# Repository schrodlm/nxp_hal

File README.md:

# Assignment 5: HAL development on S32K118

In this assignment the target platform changes from the STM32F407 to the NXP S32K118, an Arm Cortex‑M0+ microcontroller from the S32K1xx automotive family. On STM32, STM32CubeMX generated both the initialization code and a Hardware Abstraction Layer (HAL). On the S32K118, no vendor HAL is provided: you are given the CMSIS‑style register definitions and a minimal project skeleton, and the objective of this assignment is to implement the HAL yourself.

For every peripheral used in the exercises, a header file with a complete Doxygen description of the API (functions, parameters, preconditions, pin mapping) is supplied. Your task is to implement the corresponding `.c` files so that the provided example programs in `main.c` behave as specified.

---

## 0. Before you start — board preparation

> ⚠️ Before powering the board on and before flashing anything, the board jumpers must be reconfigured for the S32K118:
>
> - move the **STM** jumper to the **OFF** position (disables the STM32 side by keeping it all the time in reset);
> - move the **S32** jumper to the **RST** position (connects the reset signal on S32 to the reset button on the board).
> - connect the board via a USB-C
> Once this is done, the STM32 development board may remain physically attached to the shield — it does not interfere with the sensors/actuators.

The exact jumper locations are shown in the board schematic and in the KiCad project under [`ers-board-v1.2/`](ers-board-v1.2/). See in particular [`ers-board-v1.2/schematics.pdf`](ers-board-v1.2/schematics.pdf) and the KiCad sources under [`ers-board-v1.2/kicad/`](ers-board-v1.2/kicad/) [`210_prog_soft_start.kicad_sch`](ers-board-v1.2/kicad/210_prog_soft_start.kicad_sch) for the programmer/reset‑related jumpers, and the other sheets for the peripheral pin assignments referenced by the HAL headers.

---

## 1. Project contents

The project is self‑contained and is organized as follows (simplified):

```text
├── CMakeLists.txt              # top-level build script
├── devices/                    # CMSIS headers, startup code, linker script
│   ├── common/s32_core_cm0.h   
│   ├── S32K118/…               # register definitions, linker scripts, SVD
│   ├── device_registers.h
│   ├── callbacks.h
│   ├── devassert.h
│   ├── floats.h
│   ├── status.h
│   └── startup.c / .h
├── src/
│   ├── core/                   # provided: clock, systick, UART, syscalls
│   │   ├── clock.c / .h
│   │   ├── systick.c / .h
│   │   ├── syscalls.c / .h
│   │   ├── debug_uart.c / .h
│   │   └── system.c / .h       # system_init() convenience
│   ├── lib/                    # to be implemented: only the .h files are given
│   │   ├── led.h               # implement led.c
│   │   ├── btn.h               # implement btn.c
│   │   ├── btn_cnt.h           # implement btn_cnt.c
│   │   ├── kpad.h              # implement kpad.c
│   │   ├── enc.h               # implement enc.c
│   │   ├── servo.h             # implement servo.c
│   │   ├── spi.h               # implement spi.c
│   │   ├── lcd.h               # implement lcd.c
│   │   ├── lcd_font.c / .h     # provided (bitmap font)
│   │   ├── eeprom.h            # implement eeprom.c
│   │   ├── joy.h               # implement joy.c
│   │   └── sht40.h             # implement sht40.c
│   ├── e00_starter/main.c      # runs out-of-the-box, no HAL needed
│   ├── e01_led/main.c          # requires led.c
│   ├── e02_btn/main.c          # requires led.c, btn.c
│   ├── e03_btn_cnt/main.c      # requires led.c, btn.c, btn_cnt.c
│   ├── e04_kpad/main.c         # requires led.c, kpad.c
│   ├── e05_enc/main.c          # requires led.c, enc.c
│   ├── e06_servo/main.c        # requires led.c, enc.c, servo.c
│   ├── e07_lcd/main.c          # requires led.c, spi.c, lcd.c
│   ├── e08_eeprom/main.c       # requires led.c, spi.c, eeprom.c
│   ├── e09_joy/main.c          # requires led.c, joy.c
│   └── e10_sht/main.c          # requires several of the above and sht40.c
├── docs/                       # S32K118 reference manual and CPU documentation
└── unity/                      # Unity test framework (for the test targets)
```

Provided:

- [`devices/`](devices/) — NXP CMSIS register headers, startup code, and the GCC linker script.
- [`src/core/`](src/core/) — clock at 40 MHz, SysTick at 1 ms, debug UART (`printf` over LPUART1 at 1 Mbps), and syscalls. Calling `system_init()` performs all of this.
- [`src/lib/lcd_font.{c,h}`](src/lib/lcd_font.c) — 5×7 bitmap font used by the LCD driver.
- [`src/eXX_*/main.c`](src/) — the `main.c` of every exercise.
- [`CMakeLists.txt`](CMakeLists.txt) — all build targets, including flashing targets (`UP_*`).

To be implemented:

- One `.c` file per peripheral under [`src/lib/`](src/lib), implementing the API documented in the corresponding header. The header files contain the full specification (pin mapping, required behavior, preconditions, ISR contracts, and so on) and should be read carefully before starting.

No new `main.c` is to be written.

---

## 2. Toolchain

Two tools are required: an ARM GCC toolchain (for cross‑compilation) and OpenOCD (for flashing and debugging).

> A recent OpenOCD (version ≥ 0.12.0+dev – from 2026) is required. Older distribution packages frequently lack correct support for the S32K target. Prebuilt releases are available from <https://github.com/openocd-org/openocd/releases>.

In addition, CMake (≥ 3.20) and a build driver (Ninja is recommended; `make` is also supported) are required.

> The use of an IDE with integrated CMake support, such as CLion or Visual Studio Code (with the *CMake Tools* and *Cortex‑Debug* extensions), is strongly recommended. CLion ships its own bundled copies of CMake and Ninja, so under CLion only the ARM GCC toolchain and OpenOCD have to be installed separately. Both IDEs provide integrated support for GDB + OpenOCD debugging.

### 2.1 Windows

1. ARM GCC toolchain — install the standalone [Arm GNU Toolchain](https://developer.arm.com/downloads/-/arm-gnu-toolchain-downloads) (the `arm-none-eabi` package). Alternatively, it can be installed via the [Scoop](https://scoop.sh/) package manager: `scoop install gcc-arm-none-eabi`. Students who already have STM32CubeCLT installed from a previous assignment do not need to install anything else, since STM32CubeCLT ships `arm-none-eabi-gcc` and `arm-none-eabi-gdb` as part of its distribution.
2. OpenOCD — download the latest Windows build from the GitHub releases page listed above, extract the archive, and add its `bin/` directory to `PATH` (or invoke the executable with its full path).

### 2.2 Linux

Install the ARM GCC toolchain via your distribution's package manager (the package name varies between distributions; on Debian/Ubuntu it is `gcc-arm-none-eabi`).

---

## 3. Build system and workflow

The project uses CMake with the cross‑compilation toolchain configured directly inside `CMakeLists.txt` (which forces `arm-none-eabi-gcc` and links against the S32K118 linker script). The recommended way of working with the project is to open it as a CMake project in CLion or VS Code and let the IDE drive the configuration, build, and flashing steps.

### 3.1 Build targets

For each exercise target `eXX_name`, the build produces:

- `eXX_name.elf` — ELF file with debug symbols (consumed by GDB);
- `eXX_name.hex` — Intel HEX file (consumed by the flashing command);
- `eXX_name.map` — linker map;
- `eXX_name.asm` — full disassembly listing, useful for diagnosing subtle HAL issues.

### 3.2 Flashing the board

The development board is connected via CMSIS‑DAP over SWD. Each exercise defines an auto‑generated flashing target named `UP_<target>.elf` (for example, `UP_e00_starter.elf`). Building this target from the IDE builds the corresponding exercise, programs the flash, verifies the content, and resets the microcontroller. (The `UP_*` targets are custom CMake targets — they are *built*, not run. In CLion and VS Code, select the target from the target selector and invoke the usual *build* command.)

### 3.3 Serial output

`printf()` is routed to LPUART1 (pins PTC7/TX and PTC6/RX) at 1 Mbps, 8N1 by `debug_uart_init()`, which is invoked from `system_init()`.

A USB‑to‑UART adapter must be connected to these pins and a terminal application (for example PuTTY, Tera Term, `minicom`, `picocom`, or the VS Code *Serial Monitor* extension) configured for 1 000 000 baud, 8N1, no flow control.

### 3.4 Unit tests

Several modules (`e01_led`, `e02_btn`, `e03_btn_cnt`, `e08_eeprom`) are accompanied by a companion `test.c` that runs on the board. The tests are written against [Unity](https://www.throwtheswitch.org/unity), a small C unit‑testing framework designed for embedded targets. Each test file defines a set of `test_*` functions and registers them with `RUN_TEST(...)` inside `main`; Unity executes them sequentially, compares actual and expected values via `TEST_ASSERT_*` macros, and prints a `PASS`/`FAIL` line per test together with a summary of the whole run. The framework itself lives under `unity/` and is linked automatically into every test binary.

The corresponding binaries are exposed through the `TST_*` target prefix (for example, `UP_TST_e01_led.elf` builds and flashes the test variant of the LED exercise). Test results are printed on the debug UART. Some tests require an additional jumper wire; refer to the comments at the top of each `test.c` file for details.

### 3.5 Logging with `printf`

`printf` is the most immediate diagnostic instrument available and will be used throughout the assignment. The following points should be observed:

- Terminate each message with `\n` or call `fflush(stdout)` explicitly. The C runtime line‑buffers `stdout`, and a message without a newline may remain in the buffer and never be transmitted over the UART.
- Avoid calling `printf` from interrupt service routines. LPUART1 blocks when its transmit FIFO is full, so a verbose ISR may stall the main loop. For ISRs, either set a flag and perform the output from the main loop, or restrict the output to a single character via `debug_uart_putchar()`.
- Do not use the `%f` conversion specifier. Use integer formatting (milli‑units or fixed‑point) instead.

### 3.6 Reference documentation

Several reference PDFs are provided under `examples/s32/docs/`. You will not need to read any of them cover to cover; each one is a lookup reference for a specific layer of the stack.

- [`S32K-RM.pdf`](docs/S32K-RM.pdf) — **S32K1xx Series Reference Manual.** The primary document for this assignment. Contains the description of every peripheral (GPIO/PORT, LPSPI, LPI2C, LPUART, LPIT, ADC, FTM, DMA/DMAMUX, FlexCAN, …) and the corresponding register maps, together with the **pin‑mux (PORT alternate‑function) tables** and the **DMAMUX source tables** (which DMA request number corresponds to which peripheral). The register names used in the manual match the macros in `devices/S32K118/include/S32K118.h`, so a chapter in this PDF translates directly to the register writes you need in your `.c` file. Consult it whenever you are configuring a new peripheral, wiring a pin to an alternate function, or hooking a peripheral to a DMA channel. **Note**: the reference manuals has a number of attachments, including S32K118 IO signal description input multiplexing and S32K1xx DMA interrupt mapping as excel files. To see the attachments, open the PDF in a capable viewer (for example, Foxit PDF Reader or Acrobat Reader) and look for the attachments pane.

- [`S32K1xx.pdf`](docs/S32K1xx.pdf) — **S32K1xx Data Sheet.** Electrical characteristics, memory map overview, clock tree, and package pin assignments. Useful for the electrical/timing side of things; the functional pin‑mux information is in `S32K-RM.pdf` (see above).
- `Arm_Architecture_v6m_Reference_Manual.pdf` — **ARMv6‑M Architecture Reference Manual.** Defines the instruction set, exception model, and programmer's model of the Cortex‑M0+ core. Needed only if you want to read or understand Thumb assembly (for example, the `.asm` listing produced by the build) or when dealing with low‑level exception behavior.
- [`DDI0484C_cortex_m0p_r0p1_trm.pdf`](docs/DDI0484C_cortex_m0p_r0p1_trm.pdf) — **Cortex‑M0+ Technical Reference Manual.** Implementation‑specific documentation of the CPU core (NVIC layout, SysTick, pipeline behavior). Relevant mainly when you are configuring the NVIC (interrupt enable/priority) or SysTick — both of which are already done for you in `core/`, but are worth consulting if you add your own interrupts.
- [`DUI0662B_cortex_m0p_r0p1_dgug.pdf`](docs/DUI0662B_cortex_m0p_r0p1_dgug.pdf) — **Cortex‑M0+ Devices Generic User Guide.** A tutorial‑style companion to the TRM, written from a programmer's point of view. Often a gentler starting point when the TRM is too dense.

In short: start from the corresponding header in `src/lib/`, look up the peripheral chapter (and the pin‑mux and DMAMUX tables) in `S32K-RM.pdf` and fall back to the Cortex‑M0+ documents only for core‑side questions (interrupts, exceptions, low‑level CPU behavior).

---

## 4. How to work on an exercise

Each HAL module should be implemented one at a time and verified with the corresponding exercise program. The recommended procedure for every exercise is:

1. Open the corresponding `.h` file in `src/lib/` and read the Doxygen description in full (pin mapping, expected behavior, whether functions may be called from ISR context, notes on listeners, and so on).
2. Consult the relevant peripheral chapter in the S32K118 Reference Manual (`docs/S32K-RM.pdf`). The register names in the manual match the macros in `devices/S32K118/include/S32K118.h`.
3. Create the `.c` file in `src/lib/`. No modification to `CMakeLists.txt` is required — the top‑level `CMakeLists.txt` already references the expected filenames.
4. Build the `UP_eXX_...elf` target to flash the corresponding exercise, and verify the behavior on the board and over UART.
5. If a unit test is provided for the module (see [§ 3.4](#34-unit-tests)), flash it by building the matching `UP_TST_eXX_...elf` target and confirm that all test cases pass on the debug UART. Executing the provided tests is a mandatory part of the assignment: a module counts as correctly implemented only once its test reports all `PASS`. Any additional wiring required by the test is documented at the top of the corresponding `test.c` file.

### 4.1 Using AI assistants

You are allowed to use AI coding assistants (Copilot, ChatGPT, Claude, Gemini, …) while working on this assignment, but the following conditions apply:

- **Review every register assignment manually.** AI models are trained on a huge variety of microcontroller families, and they routinely produce code that *looks* correct but encodes subtle mistakes. Always cross‑check the generated register configuration against the corresponding chapter of `docs/S32K-RM.pdf` before trusting it, especially for PORT `PCR` (MUX field), PCC clock gates, peripheral enable bits, DMAMUX source numbers, and NVIC settings.
- **You must be able to explain every register assignment in your code.** During evaluation you may be asked to walk through any line of any peripheral configuration. You will be given the relevant register map from the Reference Manual, so you do not have to memorise the register abbreviations and bit positions — but you are expected to explain, for every `PCC->PCCn[...] = …`, every `PORT->PCR[...] = …`, every `LPSPIx->CFGRx = …`, and so on, *why* those bits are set the way they are and what the resulting hardware behavior is. "The AI wrote it" is not an acceptable answer. If you cannot explain a line, treat that as a signal to go back and read the relevant section of the Reference Manual until you can.

---

## 5. Exercises

### Exercise 0 — Starter and environment verification

Target: `e00_starter`.

Goal: verify that the complete toolchain (build, flash, serial terminal, debugger) is functional before any HAL code is written. No HAL code is required for this exercise; only the provided `core` modules are used.

Expected behavior: once flashed, the board prints one line per second on the debug UART:

```text
[0000000003] Counter 0
[0000001003] Counter 1
[0000002003] Counter 2
…
```

If the output is garbled, verify that the terminal is configured for 1 Mbps. If there is no output at all, verify that the USB‑to‑UART adapter is wired to PTC7 and PTC6 and that no other device is driving these pins.

---

### Exercise 1 — LED

Target: `e01_led`. Module: `led.c`.

Goal: implement GPIO output control for the four on‑board LEDs. Verified by `e01_led` cycling through the LEDs one at a time.

Build the `UP_TST_e01_led.elf` target to flash and execute the unit test, and confirm that all cases report `PASS` on the debug UART.

---

### Exercise 2 — Buttons

Target: `e02_btn`. Module: `btn.c`.

Goal: implement GPIO input and PORT‑interrupt handling for the four on‑board buttons. Verified by `e02_btn` printing the button state on every edge.

Build the `UP_TST_e02_btn.elf` target to flash and execute the unit test, and confirm that all cases report `PASS` on the debug UART.

---

### Exercise 3 — Button counter with debouncing

Target: `e03_btn_cnt`. Module: `btn_cnt.c`.

Goal: implement a debounced press counter on top of `btn.c` and the SysTick listener mechanism, following the state machine described in `btn_cnt.h`. Verified by `e03_btn_cnt` reporting a stable count even under rapid repeated presses.

Build the `UP_TST_e03_btn_cnt.elf` target to flash and execute the unit test, and confirm that all cases report `PASS` on the debug UART.

---

### Exercise 4 — Matrix keypad

Target: `e04_kpad`. Module: `kpad.c`.

Goal: implement scanning of the external 3×4 matrix keypad. Verified by `e04_kpad` printing the set of pressed keys whenever it changes.

---

### Exercise 5 — Rotary encoder

Target: `e05_enc`. Module: `enc.c`.

Goal: implement quadrature decoding of the rotary encoder using FTM1, plus GPIO input for the encoder push button. Verified by `e05_enc` printing the encoder position and resetting it on button press.

---

### Exercise 6 — Servo motor

Target: `e06_servo`. Module: `servo.c`.

Goal: implement 50 Hz PWM control of the SG90 servo using FTM0. Verified by `e06_servo` driving the servo from the encoder position.

---

### Exercise 7 — SPI and ST7565 LCD

Modules: `spi.c`, `lcd.c`.

Goal: implement the SPI driver for LPSPI0 and the ST7565 graphical LCD driver on top of it.

This exercise is split into two phases and should be done in order:

1. **Blocking variant — target `e07_lcd`.** Start with the blocking SPI (`spi_txrx`) and the full framebuffer‑based drawing API. The implementation busy‑waits on the LPSPI `TDF`/`RDF` flags. Verified by `e07_lcd` showing a static text pattern and animated pixels.
2. **DMA variant — target `e07_lcd-dma` (OPTIONAL, for the daring ones).** Once the blocking variant works, add the DMA path (`spi_dma_txrx` plus the asynchronous path in `lcd.c`), compiled with the `SPI_WITH_DMA` definition that the `e07_lcd-dma` target already provides. The on‑screen behavior must be identical; the difference is that the main loop stays responsive during SPI transfers. **This phase is optional** — it is significantly more involved than the blocking variant, and students may skip it and move on to exercise 8.

Read `spi.h` carefully before starting the DMA phase — especially the instructions on the buffer alignment and byte‑swap.

#### How to build the DMA path

The DMA variant offloads the entire transfer to eDMA + LPSPI, so `spi_dma_txrx()` can return immediately and the caller is notified later via a callback. Before starting, read `spi.h` in full — it fixes the observable contract (non‑blocking semantics, 4‑byte buffer alignment, byte swap, split TX/RX callbacks). The implementation can then proceed roughly as follows:

1. **Two DMA channels.** Allocate one channel for TX (source = memory buffer, destination = `LPSPI0->TDR`) and one for RX (source = `LPSPI0->RDR`, destination = memory buffer). Route the LPSPI0 TX and RX requests to them via DMAMUX (sources 15 and 14) and enable LPSPI's DMA request generation with `DER = TDDE | RDDE`.

2. **4‑byte transfer granularity.** Program the eDMA TCDs with `SSIZE = DSIZE = 2` (meaning 2² = 4 bytes) and `NBYTES = 4`. The major‑loop iteration count is `count / 4`. This is why `spi.h` requires buffers aligned to 4 bytes.

3. **Byte swap.** The Cortex‑M0+ is little‑endian, but LPSPI shifts out `TDR` MSB‑first. Setting `LPSPI_TCR_BYSW = 1` reverses the byte order inside each 32‑bit transfer, so the bytes appear on the wire in the same order as they sit in memory.

4. **Frame size.** `LPSPI_TCR_FRAMESZ = count * 8 − 1` controls exactly how many bits are clocked. A byte count that is not a multiple of 4 therefore stops in the middle of the last word; the tail (`count & 3` bytes) is handled differently on TX and RX:

   - **TX tail — scatter‑gather.** Prepare a second TCD (statically allocated, 32‑byte aligned) that transfers a single 32‑bit word from a small staging variable into `TDR`. Before starting the transfer, copy the `rem = count & 3` tail bytes into that staging word *right‑aligned*, so that after the byte swap they clock out in the correct order. Link the two TCDs by setting the main TCD's `DLASTSGA` to the address of the tail TCD and `CSR.ESG = 1`; when the main major loop finishes, eDMA automatically switches to the tail TCD. When `count` is a multiple of 4, scatter‑gather is disabled and `CSR.DREQ = 1` stops the channel cleanly after the major loop.

   - **RX tail — LPSPI Frame‑Complete IRQ.** The RX DMA channel only receives a request once a full 32‑bit word is in the RX FIFO, and so it will never service the tail. Enable the LPSPI frame‑complete interrupt (`IER.FCIE = 1`) and, inside the ISR, read `LPSPI0->RDR` once and un‑swap the remaining bytes into the caller's RX buffer.

5. **Completion callbacks.** Two callbacks are delivered independently, matching the `spi.h` contract:
   - The TX callback is fired from the LPSPI frame‑complete ISR.
   - The RX callback is fired from the DMA major‑loop interrupt on the RX channel (enable it with `CSR.INTMAJOR = 1`) when `count % 4 == 0`; otherwise it is fired from the LPSPI frame‑complete ISR after the tail has been drained.

6. **Idle tracking.** Keep two independent idle flags (TX, RX); each becomes false when its side is queued and true again only once its callback has been invoked. `spi_is_idle()` returns the conjunction; `spi_dma_txrx()` refuses a new request if either side is still busy.

The LCD driver on top of this must become asynchronous as well: `lcd_update()` starts a DMA transfer and returns immediately, and the DC and CS lines must be toggled inside the callbacks (not inline after `spi_dma_txrx()`), since at that point no bit has yet left the shift register. The header shows the callback‑chaining pattern to use.

---

### Exercise 8 — SPI EEPROM (M95080)

Target: `e08_eeprom`. Module: `eeprom.c`.

Goal: implement page‑level read and write access to the M95080 SPI EEPROM, including WIP polling. Verified by `e08_eeprom` writing a test pattern to page 0, reading it back, and turning the green LED on if the contents match (red otherwise).

Build the `UP_TST_e08_eeprom.elf` target to flash and execute the unit test, and confirm that all cases report `PASS` on the debug UART.

---

### Exercise 9 — Analog joystick

Target: `e09_joy`. Module: `joy.c`.

Goal: implement 12‑bit ADC conversions of the joystick X/Y channels on ADC0, plus the push‑button GPIO. Verified by `e09_joy` streaming the joystick state over UART.

---

### Exercise 10 — SHT40 temperature and humidity sensor

Target: `e10_sht`. Module: `sht40.c`.

Goal: implement the SHT40 driver over LPI2C0 with periodic, asynchronous measurements triggered by LPIT channel 0. Verified by `e10_sht`, which integrates the sensor with the LCD and EEPROM from the earlier exercises: the current and min/max temperature/humidity are displayed on the LCD and persisted across reset.

## Cookbook
Please refer to the [cookbook](docs/AN5413.pdf) for examples of how to use registers to configure and how to use peripherals.

The book references a repo with example code, which has moved to the following location:
https://github.com/nxp-auto-support/s32k118_cookbook

---

## Submission

Submit your solution in the `assignment5/` folder of your course GitLab repository. For each implemented module, include the `.c` file (and any other files that have been modified). The `build-debug/` and `build-release/` directories should not be committed.

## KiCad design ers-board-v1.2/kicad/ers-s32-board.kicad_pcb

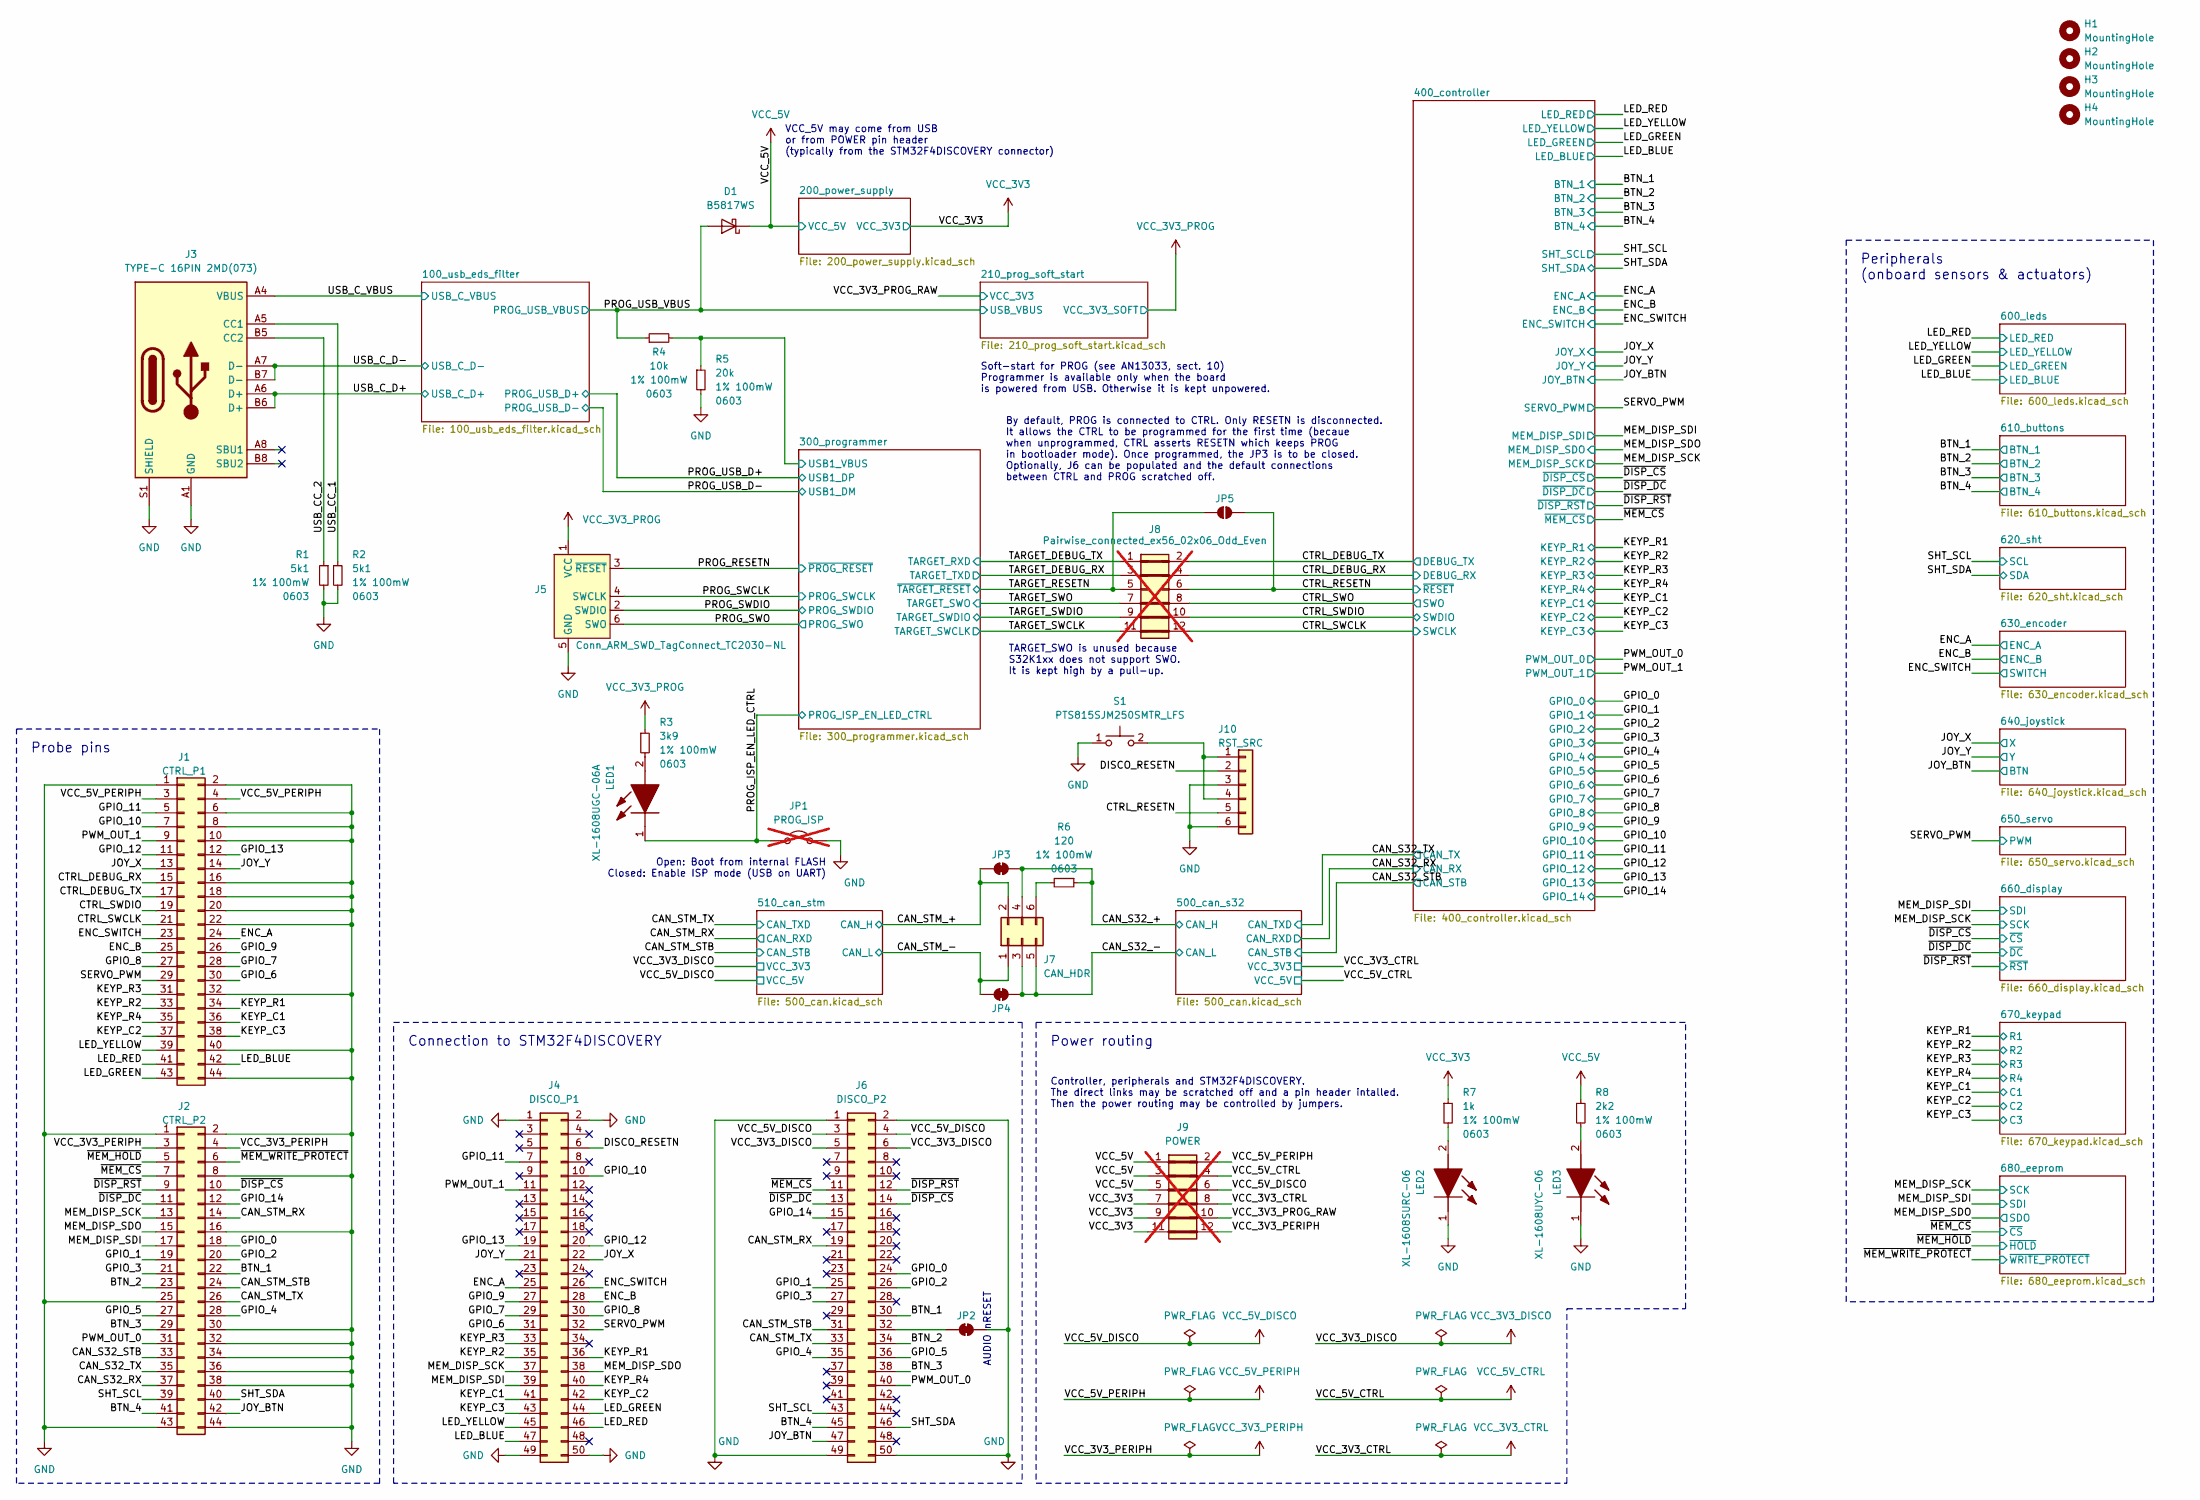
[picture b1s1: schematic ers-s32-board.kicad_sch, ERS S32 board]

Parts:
D1: B5817WS; D_SOD-323; Mouser 771-PMEG4005EJ-T/R
H1, H2, H3, H4: MountingHole; MountingHole_3mm
J1: CTRL_P1; PinHeader_2x22_P2.54mm_Vertical; JLCPCB Part C725894
J2: CTRL_P2; PinHeader_2x22_P2.54mm_Vertical; JLCPCB Part C725894
J3: TYPE-C 16PIN 2MD(073); JLCPCB Part C2765186
J4: DISCO_P1; DISCO_Socket; JLCPCB Part C7499355
J5: Conn_ARM_SWD_TagConnect_TC2030-NL; Tag-Connect_TC2030-IDC-NL_2x03_P1.27mm_Vertical
J6: DISCO_P2; DISCO_Socket; JLCPCB Part C7499355
J7: CAN_HDR; PinHeader_2x03_P2.54mm_Vertical
J8: Pairwise_connected_ex56_02x06_Odd_Even; Pairwise_Connected_ex56_PinHeader_2x06_P2.54mm_Vertical; not fitted
J9: POWER; Pairwise_Connected_PinHeader_2x06_P2.54mm_Vertical; not fitted
J10: RST_SRC; PinHeader_1x06_P2.54mm_Vertical; JLCPCB Part C2937625
JP1: PROG_ISP; PinHeader_1x02_P2.54mm_Vertical; JLCPCB Part C492401; not fitted
JP2, JP3, JP4: SolderJumper_2_Bridged; SolderJumper-2_P1.3mm_Bridged_RoundedPad1.0x1.5mm
JP5: SolderJumper_2_Open; SolderJumper-2_P1.3mm_Open_TrianglePad1.0x1.5mm
LED1: XL-1608UGC-06A; XL-1608_LED_0603; JLCPCB Part C7371903
LED2: XL-1608SURC-06; XL-1608_LED_0603; JLCPCB Part C965799
LED3: XL-1608UYC-06; XL-1608_LED_0603; JLCPCB Part C965802
R1, R2: 5k1; R_0603_1608Metric_Pad0.98x0.95mm_HandSolder; Mouser 303-0603WAF5101T5E
R3: 3k9; R_0603_1608Metric_Pad0.98x0.95mm_HandSolder; JLCPCB Part C23018
R4: 10k; R_0603_1608Metric_Pad0.98x0.95mm_HandSolder; JLCPCB Part C25804
R5: 20k; R_0603_1608Metric_Pad0.98x0.95mm_HandSolder; JLCPCB Part C4184
R6: 120; R_0603_1608Metric_Pad0.98x0.95mm_HandSolder; JLCPCB Part C22787
R7: 1k; R_0603_1608Metric_Pad0.98x0.95mm_HandSolder; JLCPCB Part C21190
R8: 2k2; R_0603_1608Metric_Pad0.98x0.95mm_HandSolder; JLCPCB Part C4190
S1: PTS815SJM250SMTR_LFS; Mouser 611-PTS815SJM250SMTR

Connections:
/300_programmer/USB1_VBUS: R4.2, R5.1; also elsewhere on the board
/BTN_1: J2.22, J6.30; also elsewhere on the board
/BTN_2: J2.23, J6.34; also elsewhere on the board
/BTN_3: J2.29, J6.38; also elsewhere on the board
/BTN_4: J2.41, J6.45; also elsewhere on the board
/CAN_S32_+: J7.4, JP3.2 (B), R6.1; also elsewhere on the board
/CAN_S32_-: J7.3, J7.5, JP4.2 (B); also elsewhere on the board
/CAN_S32_RX: J2.37; also elsewhere on the board
/CAN_S32_STB: J2.33; also elsewhere on the board
/CAN_S32_TX: J2.35; also elsewhere on the board
/CAN_STM_+: J7.2, JP3.1 (A); also elsewhere on the board
/CAN_STM_-: J7.1, JP4.1 (A); also elsewhere on the board
/CAN_STM_RX: J2.14, J6.19; also elsewhere on the board
/CAN_STM_STB: J2.24, J6.31; also elsewhere on the board
/CAN_STM_TX: J2.26, J6.33; also elsewhere on the board
/CTRL_DEBUG_RX: J1.15, J8.4; also elsewhere on the board
/CTRL_DEBUG_TX: J1.17, J8.2; also elsewhere on the board
/CTRL_RESETN: J8.6, J10.5, JP5.2 (B); also elsewhere on the board
/CTRL_SWCLK: J1.21, J8.12; also elsewhere on the board
/CTRL_SWDIO: J1.19, J8.10; also elsewhere on the board
/CTRL_SWO: J8.8; also elsewhere on the board
/DISCO_RESETN: J4.6, J10.2
/ENC_A: J1.24, J4.25; also elsewhere on the board
/ENC_B: J1.25, J4.28; also elsewhere on the board
/ENC_SWITCH: J1.23, J4.26; also elsewhere on the board
/GPIO_0: J2.18, J6.24; also elsewhere on the board
/GPIO_1: J2.19, J6.25; also elsewhere on the board
/GPIO_2: J2.20, J6.26; also elsewhere on the board
/GPIO_3: J2.21, J6.27; also elsewhere on the board
/GPIO_4: J2.28, J6.35; also elsewhere on the board
/GPIO_5: J2.27, J6.36; also elsewhere on the board
/GPIO_6: J1.30, J4.31; also elsewhere on the board
/GPIO_7: J1.28, J4.29; also elsewhere on the board
/GPIO_8: J1.27, J4.30; also elsewhere on the board
/GPIO_9: J1.26, J4.27; also elsewhere on the board
/GPIO_10: J1.7, J4.10; also elsewhere on the board
/GPIO_11: J1.5, J4.7; also elsewhere on the board
/GPIO_12: J1.11, J4.20; also elsewhere on the board
/GPIO_13: J1.12, J4.19; also elsewhere on the board
/GPIO_14: J2.12, J6.15; also elsewhere on the board
/JOY_BTN: J2.42, J6.47; also elsewhere on the board
/JOY_X: J1.13, J4.22; also elsewhere on the board
/JOY_Y: J1.14, J4.21; also elsewhere on the board
/KEYP_C1: J1.36, J4.41; also elsewhere on the board
/KEYP_C2: J1.37, J4.42; also elsewhere on the board
/KEYP_C3: J1.38, J4.43; also elsewhere on the board
/KEYP_R1: J1.34, J4.36; also elsewhere on the board
/KEYP_R2: J1.33, J4.35; also elsewhere on the board
/KEYP_R3: J1.31, J4.33; also elsewhere on the board
/KEYP_R4: J1.35, J4.40; also elsewhere on the board
/LED_BLUE: J1.42, J4.47; also elsewhere on the board
/LED_GREEN: J1.43, J4.44; also elsewhere on the board
/LED_RED: J1.41, J4.46; also elsewhere on the board
/LED_YELLOW: J1.39, J4.45; also elsewhere on the board
/MEM_DISP_SCK: J2.13, J4.37; also elsewhere on the board
/MEM_DISP_SDI: J2.17, J4.39; also elsewhere on the board
/MEM_DISP_SDO: J2.15, J4.38; also elsewhere on the board
/PROG_ISP_EN_LED_CTRL: JP1.1 (A), LED1.1 (K); also elsewhere on the board
/PROG_RESETN: J5.3 (~RESET); also elsewhere on the board
/PROG_SWCLK: J5.4 (SWCLK); also elsewhere on the board
/PROG_SWDIO: J5.2 (SWDIO); also elsewhere on the board
/PROG_SWO: J5.6 (SWO); also elsewhere on the board
/PROG_USB_D+: J3.A6 (D+), J3.B6 (D+); also elsewhere on the board
/PROG_USB_D-: J3.A7 (D-), J3.B7 (D-); also elsewhere on the board
/PROG_USB_VBUS: D1.2 (A), R4.1; also elsewhere on the board
/PWM_OUT_0: J2.31, J6.40; also elsewhere on the board
/PWM_OUT_1: J1.9, J4.11; also elsewhere on the board
/SERVO_PWM: J1.29, J4.32; also elsewhere on the board
/SHT_SCL: J2.39, J6.43; also elsewhere on the board
/SHT_SDA: J2.40, J6.46; also elsewhere on the board
/TARGET_DEBUG_RX: J8.3; also elsewhere on the board
/TARGET_DEBUG_TX: J8.1; also elsewhere on the board
/TARGET_RESETN: J8.5, JP5.1 (A); also elsewhere on the board
/TARGET_SWCLK: J8.11; also elsewhere on the board
/TARGET_SWDIO: J8.9; also elsewhere on the board
/TARGET_SWO: J8.7; also elsewhere on the board
/USB_CC_1: J3.A5 (CC1), R2.1
/USB_CC_2: J3.B5 (CC2), R1.1
/USB_C_VBUS: J3.A4 (VBUS), J3.A9 (VBUS), J3.B4 (VBUS), J3.B9 (VBUS); also elsewhere on the board
/VCC_3V3_PROG_RAW: J9.10; also elsewhere on the board
/~DISP_CS: J2.10, J6.14; also elsewhere on the board
/~DISP_DC: J2.11, J6.13; also elsewhere on the board
/~DISP_RST: J2.9, J6.12; also elsewhere on the board
/~MEM_CS: J2.7, J6.11; also elsewhere on the board
/~MEM_HOLD: J2.5; also elsewhere on the board
/~MEM_WRITE_PROTECT: J2.6; also elsewhere on the board
GND: J1.1, J1.2, J1.6, J1.8, J1.10, J1.16, J1.18, J1.20, J1.22, J1.32, J1.40, J1.44, J2.1, J2.2, J2.8, J2.16, J2.25, J2.30, J2.32, J2.34, J2.36, J2.38, J2.43, J2.44, J3.A1 (GND), J3.A12 (GND), J3.B1 (GND), J3.B12 (GND), J3.S1 (SHIELD), J4.1, J4.2, J4.49, J4.50, J5.5 (GND), J6.1, J6.2, J6.49, J6.50, J10.3, J10.6, JP1.2 (B), JP2.2 (B), LED2.1 (K), LED3.1 (K), R1.2, R2.2, R5.2, S1.1; also elsewhere on the board
unnamed: J6.32, JP2.1 (A)
unnamed: J7.6, R6.2
unnamed: J10.1, J10.4, S1.2
unnamed: LED1.2 (A), R3.2
unnamed: LED2.2 (A), R7.2
unnamed: LED3.2 (A), R8.2
VCC_3V3: J9.7, J9.9, J9.11, R7.1; also elsewhere on the board
VCC_3V3_CTRL: J9.8; also elsewhere on the board
VCC_3V3_DISCO: J6.5, J6.6; also elsewhere on the board
VCC_3V3_PERIPH: J2.3, J2.4, J9.12; also elsewhere on the board
VCC_3V3_PROG: J5.1 (VCC), R3.1; also elsewhere on the board
VCC_5V: D1.1 (K), J9.1, J9.3, J9.5, R8.1; also elsewhere on the board
VCC_5V_CTRL: J9.4; also elsewhere on the board
VCC_5V_DISCO: J6.3, J6.4, J9.6; also elsewhere on the board
VCC_5V_PERIPH: J1.3, J1.4, J9.2; also elsewhere on the board

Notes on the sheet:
Soft-start for PROG (see AN13033, sect. 10) Programmer is available only when the board is powered from USB. Otherwise it is kept unpowered.
Power routing
Controller, peripherals and STM32F4DISCOVERY. The direct links may be scratched off and a pin header intalled. Then the power routing may be controlled by jumpers.
VCC_5V may come from USB or from POWER pin header (typically from the STM32F4DISCOVERY connector)
TARGET_SWO is unused because S32K1xx does not support SWO. It is kept high by a pull-up.
By default, PROG is connected to CTRL. Only RESETN is disconnected. It allows the CTRL to be programmed for the first time (becaue when unprogrammed, CTRL asserts RESETN which keeps PROG in bootloader mode). Once programmed, the JP3 is to be closed. Optionally, J6 can be populated and the default c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
Open: Boot from internal FLASH Closed: Enable ISP mode (USB on UART)
Probe pins
Peripherals (onboard sensors & actuators)
AUDIO nRESET
Connection to STM32F4DISCOVERY

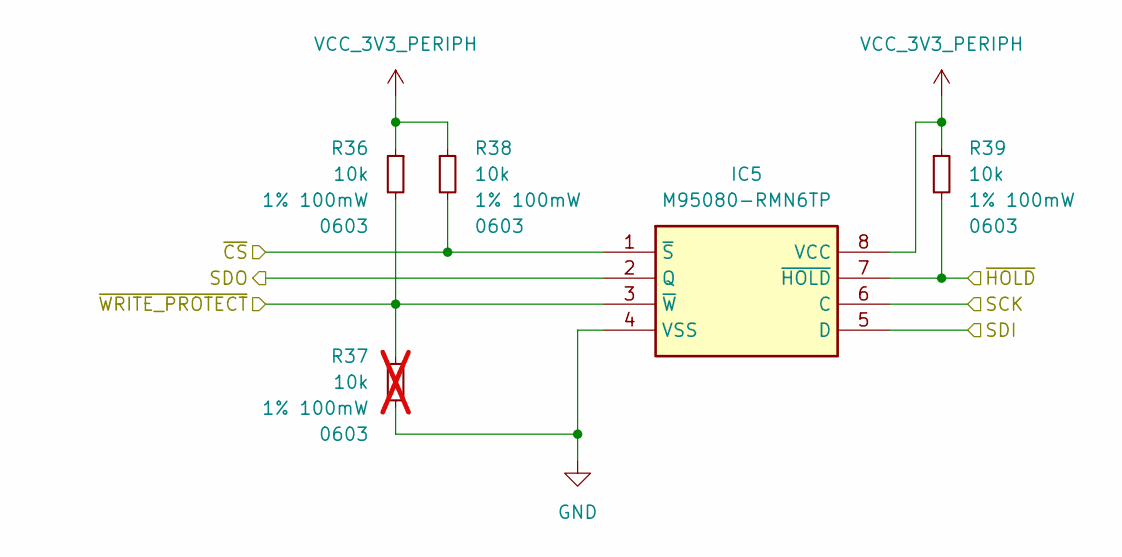
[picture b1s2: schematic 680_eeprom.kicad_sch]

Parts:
IC5: M95080-RMN6TP; Mouser 511-M95080-RMN6TP
R36, R38, R39: 10k; R_0603_1608Metric_Pad0.98x0.95mm_HandSolder; JLCPCB Part C25804
R37: 10k; R_0603_1608Metric_Pad0.98x0.95mm_HandSolder; JLCPCB Part C25804; not fitted

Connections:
/MEM_DISP_SCK: IC5.6 (C); also elsewhere on the board
/MEM_DISP_SDI: IC5.5 (D); also elsewhere on the board
/MEM_DISP_SDO: IC5.2 (Q); also elsewhere on the board
/~MEM_CS: IC5.1 (~S), R38.2; also elsewhere on the board
/~MEM_HOLD: IC5.7 (~HOLD), R39.2; also elsewhere on the board
/~MEM_WRITE_PROTECT: IC5.3 (~W), R36.2, R37.1; also elsewhere on the board
GND: IC5.4 (VSS), R37.2; also elsewhere on the board
VCC_3V3_PERIPH: IC5.8 (VCC), R36.1, R38.1, R39.1; also elsewhere on the board

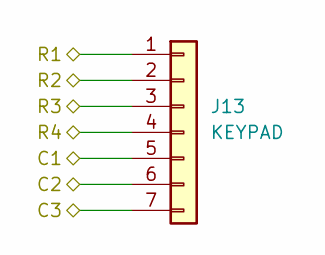
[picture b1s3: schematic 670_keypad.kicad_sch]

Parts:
J13: KEYPAD; PinHeader_1x07_P2.54mm_Horizontal; JLCPCB Part C492415

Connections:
/KEYP_C1: J13.5; also elsewhere on the board
/KEYP_C2: J13.6; also elsewhere on the board
/KEYP_C3: J13.7; also elsewhere on the board
/KEYP_R1: J13.1; also elsewhere on the board
/KEYP_R2: J13.2; also elsewhere on the board
/KEYP_R3: J13.3; also elsewhere on the board
/KEYP_R4: J13.4; also elsewhere on the board

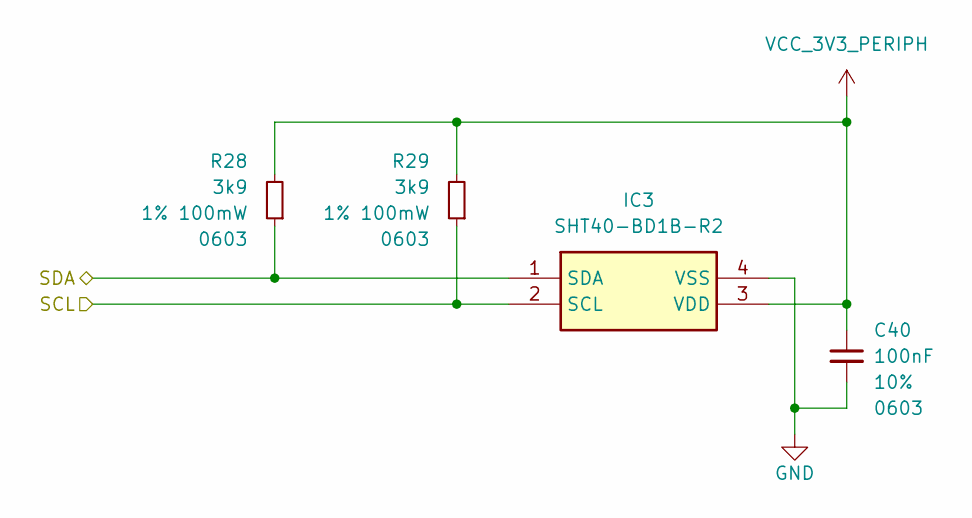
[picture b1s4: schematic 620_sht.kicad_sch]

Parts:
C40: 100nF; C_0603_1608Metric_Pad1.08x0.95mm_HandSolder; JLCPCB Part C14663
IC3: SHT40-BD1B-R2; Mouser 403-SHT40-BD1B-R2
R28, R29: 3k9; R_0603_1608Metric_Pad0.98x0.95mm_HandSolder; JLCPCB Part C23018

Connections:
/SHT_SCL: IC3.2 (SCL), R29.1; also elsewhere on the board
/SHT_SDA: IC3.1 (SDA), R28.1; also elsewhere on the board
GND: C40.2, IC3.4 (VSS); also elsewhere on the board
VCC_3V3_PERIPH: C40.1, IC3.3 (VDD), R28.2, R29.2; also elsewhere on the board

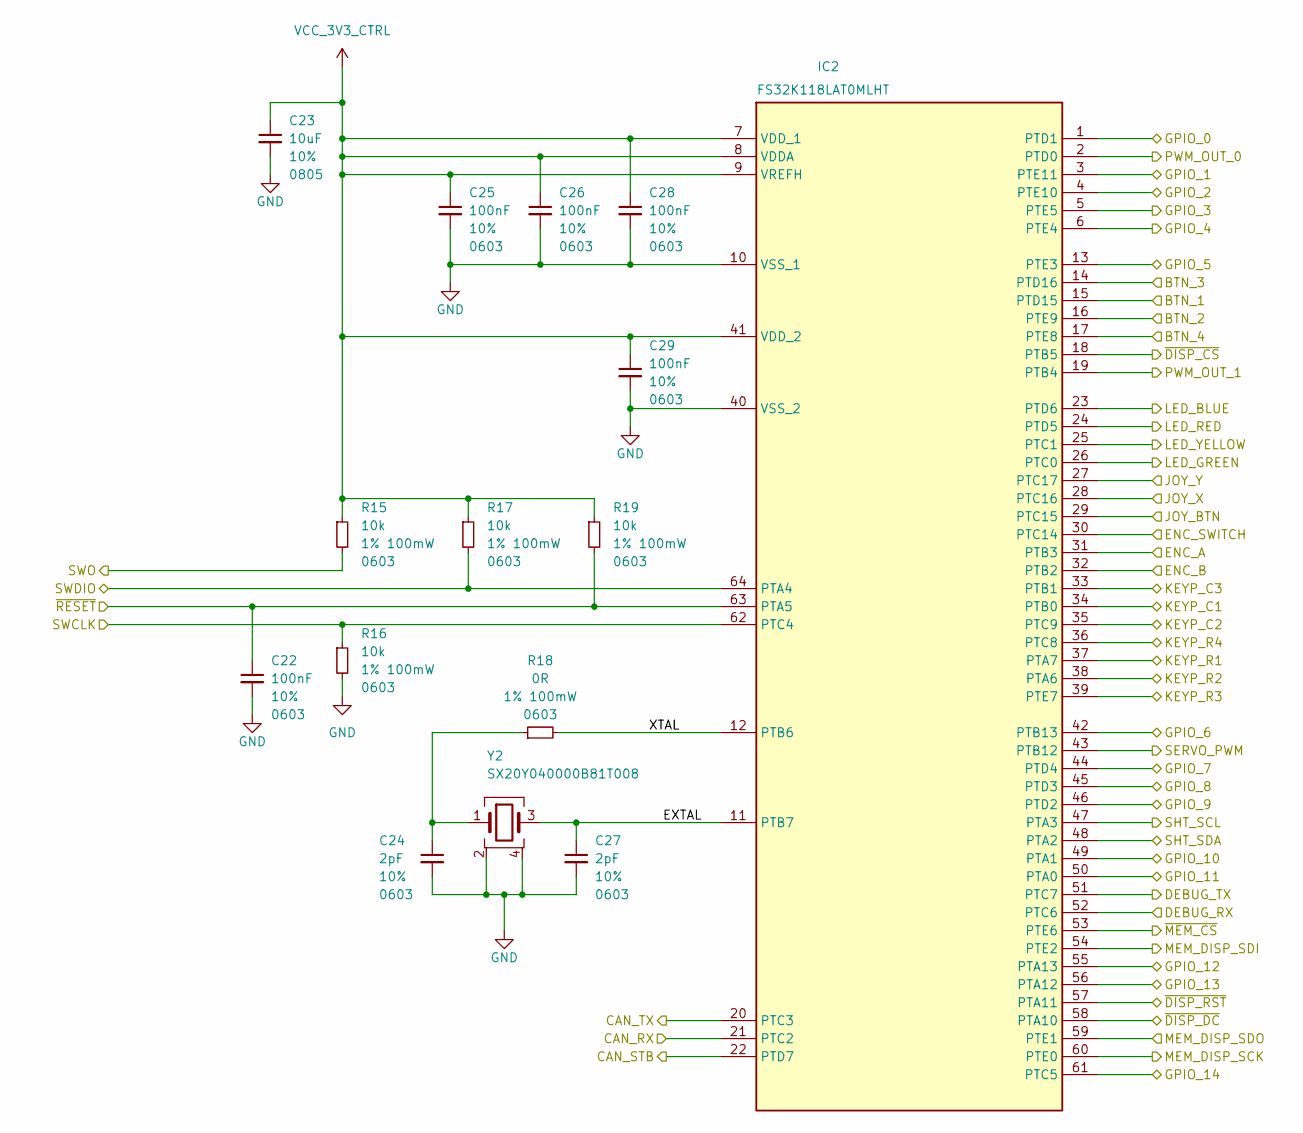
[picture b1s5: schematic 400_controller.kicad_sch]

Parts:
C22, C25, C26, C28, C29: 100nF; C_0603_1608Metric_Pad1.08x0.95mm_HandSolder; JLCPCB Part C14663
C23: 10uF; C_0805_2012Metric_Pad1.18x1.45mm_HandSolder; JLCPCB Part C15850
C24, C27: 2pF; C_0603_1608Metric_Pad1.08x0.95mm_HandSolder; JLCPCB Part C507410
IC2: FS32K118LAT0MLHT; Mouser 771-FS32K118LAT0MLHT
R15, R16, R17, R19: 10k; R_0603_1608Metric_Pad0.98x0.95mm_HandSolder; JLCPCB Part C25804
R18: 0R; R_0603_1608Metric_Pad0.98x0.95mm_HandSolder; JLCPCB Part C21189
Y2: SX20Y040000B81T008; Crystal_SMD_2016-4Pin_2.0x1.6mm; JLCPCB Part C20623610

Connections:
/400_controller/EXTAL: C27.1, IC2.11 (PTB7), Y2.3
/400_controller/XTAL: IC2.12 (PTB6), R18.2
/BTN_1: IC2.15 (PTD15); also elsewhere on the board
/BTN_2: IC2.16 (PTE9); also elsewhere on the board
/BTN_3: IC2.14 (PTD16); also elsewhere on the board
/BTN_4: IC2.17 (PTE8); also elsewhere on the board
/CAN_S32_RX: IC2.21 (PTC2); also elsewhere on the board
/CAN_S32_STB: IC2.22 (PTD7); also elsewhere on the board
/CAN_S32_TX: IC2.20 (PTC3); also elsewhere on the board
/CTRL_DEBUG_RX: IC2.52 (PTC6); also elsewhere on the board
/CTRL_DEBUG_TX: IC2.51 (PTC7); also elsewhere on the board
/CTRL_RESETN: C22.1, IC2.63 (PTA5), R19.2; also elsewhere on the board
/CTRL_SWCLK: IC2.62 (PTC4), R16.1; also elsewhere on the board
/CTRL_SWDIO: IC2.64 (PTA4), R17.2; also elsewhere on the board
/CTRL_SWO: R15.2; also elsewhere on the board
/ENC_A: IC2.31 (PTB3); also elsewhere on the board
/ENC_B: IC2.32 (PTB2); also elsewhere on the board
/ENC_SWITCH: IC2.30 (PTC14); also elsewhere on the board
/GPIO_0: IC2.1 (PTD1); also elsewhere on the board
/GPIO_1: IC2.3 (PTE11); also elsewhere on the board
/GPIO_2: IC2.4 (PTE10); also elsewhere on the board
/GPIO_3: IC2.5 (PTE5); also elsewhere on the board
/GPIO_4: IC2.6 (PTE4); also elsewhere on the board
/GPIO_5: IC2.13 (PTE3); also elsewhere on the board
/GPIO_6: IC2.42 (PTB13); also elsewhere on the board
/GPIO_7: IC2.44 (PTD4); also elsewhere on the board
/GPIO_8: IC2.45 (PTD3); also elsewhere on the board
/GPIO_9: IC2.46 (PTD2); also elsewhere on the board
/GPIO_10: IC2.49 (PTA1); also elsewhere on the board
/GPIO_11: IC2.50 (PTA0); also elsewhere on the board
/GPIO_12: IC2.55 (PTA13); also elsewhere on the board
/GPIO_13: IC2.56 (PTA12); also elsewhere on the board
/GPIO_14: IC2.61 (PTC5); also elsewhere on the board
/JOY_BTN: IC2.29 (PTC15); also elsewhere on the board
/JOY_X: IC2.28 (PTC16); also elsewhere on the board
/JOY_Y: IC2.27 (PTC17); also elsewhere on the board
/KEYP_C1: IC2.34 (PTB0); also elsewhere on the board
/KEYP_C2: IC2.35 (PTC9); also elsewhere on the board
/KEYP_C3: IC2.33 (PTB1); also elsewhere on the board
/KEYP_R1: IC2.37 (PTA7); also elsewhere on the board
/KEYP_R2: IC2.38 (PTA6); also elsewhere on the board
/KEYP_R3: IC2.39 (PTE7); also elsewhere on the board
/KEYP_R4: IC2.36 (PTC8); also elsewhere on the board
/LED_BLUE: IC2.23 (PTD6); also elsewhere on the board
/LED_GREEN: IC2.26 (PTC0); also elsewhere on the board
/LED_RED: IC2.24 (PTD5); also elsewhere on the board
/LED_YELLOW: IC2.25 (PTC1); also elsewhere on the board
/MEM_DISP_SCK: IC2.60 (PTE0); also elsewhere on the board
/MEM_DISP_SDI: IC2.54 (PTE2); also elsewhere on the board
/MEM_DISP_SDO: IC2.59 (PTE1); also elsewhere on the board
/PWM_OUT_0: IC2.2 (PTD0); also elsewhere on the board
/PWM_OUT_1: IC2.19 (PTB4); also elsewhere on the board
/SERVO_PWM: IC2.43 (PTB12); also elsewhere on the board
/SHT_SCL: IC2.47 (PTA3); also elsewhere on the board
/SHT_SDA: IC2.48 (PTA2); also elsewhere on the board
/~DISP_CS: IC2.18 (PTB5); also elsewhere on the board
/~DISP_DC: IC2.58 (PTA10); also elsewhere on the board
/~DISP_RST: IC2.57 (PTA11); also elsewhere on the board
/~MEM_CS: IC2.53 (PTE6); also elsewhere on the board
GND: C22.2, C23.2, C24.2, C25.2, C26.2, C27.2, C28.2, C29.2, IC2.10 (VSS_1), IC2.40 (VSS_2), R16.2, Y2.2, Y2.4; also elsewhere on the board
unnamed: C24.1, R18.1, Y2.1
VCC_3V3_CTRL: C23.1, C25.1, C26.1, C28.1, C29.1, IC2.7 (VDD_1), IC2.8 (VDDA), IC2.9 (VREFH), IC2.41 (VDD_2), R15.1, R17.1, R19.1; also elsewhere on the board

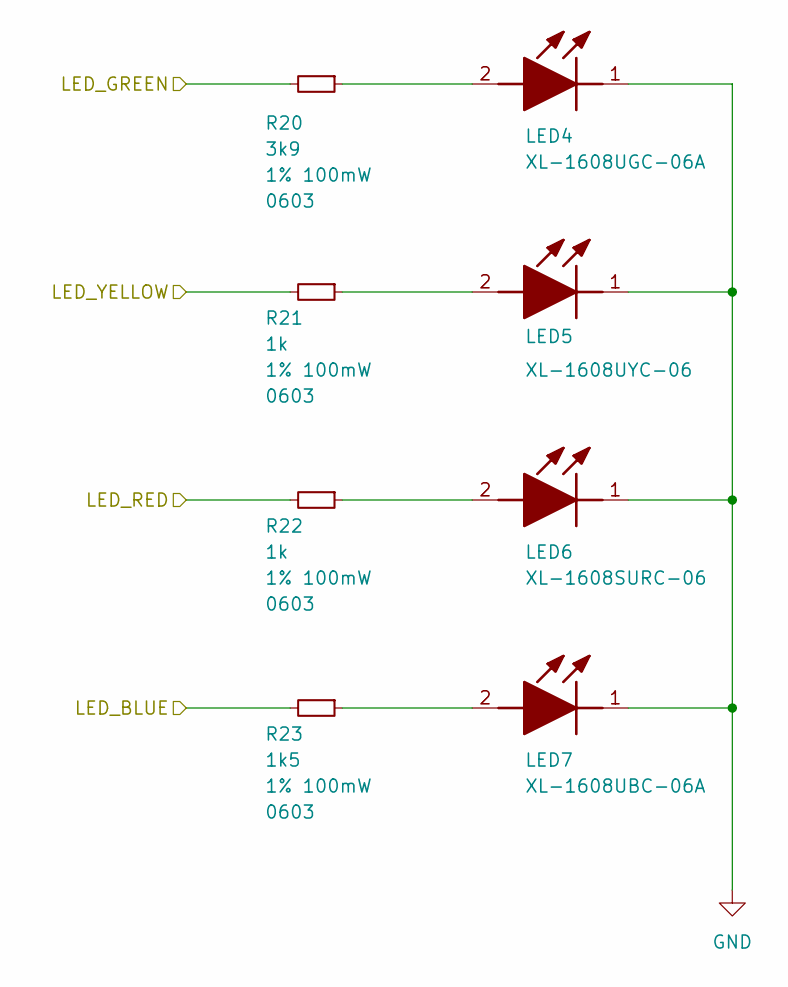
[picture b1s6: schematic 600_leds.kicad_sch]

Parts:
LED4: XL-1608UGC-06A; XL-1608_LED_0603; JLCPCB Part C7371903
LED5: XL-1608UYC-06; XL-1608_LED_0603; JLCPCB Part C965802
LED6: XL-1608SURC-06; XL-1608_LED_0603; JLCPCB Part C965799
LED7: XL-1608UBC-06A; XL-1608_LED_0603; JLCPCB Part C7371904
R20: 3k9; R_0603_1608Metric_Pad0.98x0.95mm_HandSolder; JLCPCB Part C23018
R21, R22: 1k; R_0603_1608Metric_Pad0.98x0.95mm_HandSolder; JLCPCB Part C21190
R23: 1k5; R_0603_1608Metric_Pad0.98x0.95mm_HandSolder; JLCPCB Part C22843

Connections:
/LED_BLUE: R23.2; also elsewhere on the board
/LED_GREEN: R20.2; also elsewhere on the board
/LED_RED: R22.2; also elsewhere on the board
/LED_YELLOW: R21.2; also elsewhere on the board
GND: LED4.1 (K), LED5.1 (K), LED6.1 (K), LED7.1 (K); also elsewhere on the board
unnamed: LED4.2 (A), R20.1
unnamed: LED5.2 (A), R21.1
unnamed: LED6.2 (A), R22.1
unnamed: LED7.2 (A), R23.1

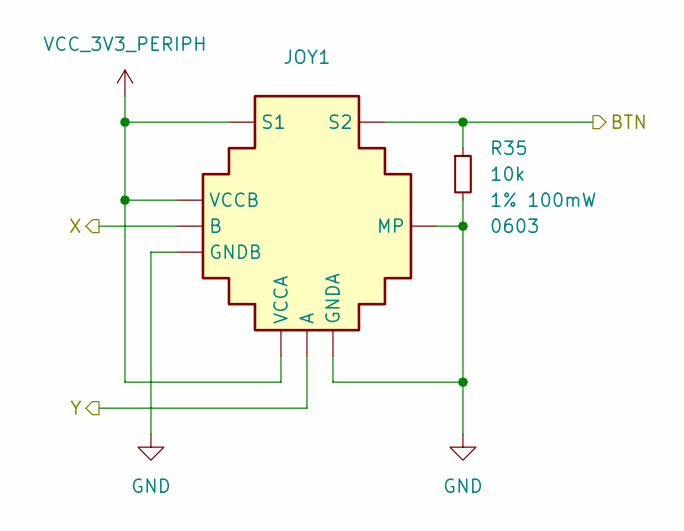
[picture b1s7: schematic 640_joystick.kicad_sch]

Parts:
JOY1: JOYSTICK_THUMB
R35: 10k; R_0603_1608Metric_Pad0.98x0.95mm_HandSolder; JLCPCB Part C25804

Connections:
/JOY_BTN: JOY1.S2, R35.1; also elsewhere on the board
/JOY_X: JOY1.B; also elsewhere on the board
/JOY_Y: JOY1.A; also elsewhere on the board
GND: JOY1.GNDA, JOY1.GNDB, JOY1.MP, R35.2; also elsewhere on the board
VCC_3V3_PERIPH: JOY1.S1, JOY1.VCCA, JOY1.VCCB; also elsewhere on the board

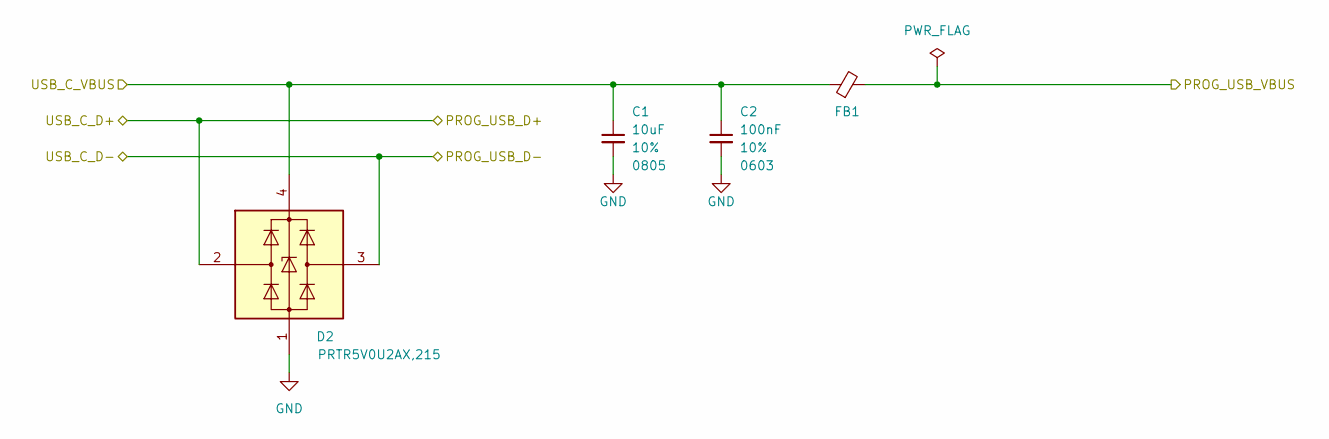
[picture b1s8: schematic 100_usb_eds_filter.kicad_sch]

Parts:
C1: 10uF; C_0805_2012Metric_Pad1.18x1.45mm_HandSolder; JLCPCB Part C15850
C2: 100nF; C_0603_1608Metric_Pad1.08x0.95mm_HandSolder; JLCPCB Part C14663
D2: PRTR5V0U2AX,215; Mouser 771-PRTR5V0U2AX-T/R
FB1: BLM18KG601SN1D; L_0603_1608Metric_Pad1.05x0.95mm_HandSolder; JLCPCB Part C85833

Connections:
/PROG_USB_D+: D2.2 (I/O1); also elsewhere on the board
/PROG_USB_D-: D2.3 (I/O2); also elsewhere on the board
/PROG_USB_VBUS: FB1.2; also elsewhere on the board
/USB_C_VBUS: C1.1, C2.1, D2.4 (VCC), FB1.1; also elsewhere on the board
GND: C1.2, C2.2, D2.1 (GND); also elsewhere on the board
